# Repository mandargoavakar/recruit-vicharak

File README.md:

Discrete Class D Audio Amplifier Design
Project Overview
This project involves the design, simulation, and PCB layout of a Class D Audio Amplifier using discrete components. The circuit utilizes an NE555 timer for PWM generation and an LM741 Op-Amp as a comparator to process audio signals.
1. Circuit Design & Logic
The amplifier operates on the principle of Pulse Width Modulation (PWM) to achieve high efficiency.
·	PWM Generation (NE555): The NE555 timer is configured as an astable multivibrator to generate a high-frequency carrier wave. With $R_1=1\text{k}\Omega$, $R_2=3.3\text{k}\Omega$, and $C_1=1\text{nF}$, the switching frequency is approximately 180kHz, well above the human hearing range.
·	Comparator Stage (LM741): The LM741 compares the $1\text{kHz}$ audio input against the high-frequency carrier wave to produce a PWM signal where the pulse width is proportional to the audio amplitude.
·	Low-Pass LC Filter: A second-order filter consisting of a $22\mu\text{H}$ inductor ($L_1$) and a $1\mu\text{F}$ capacitor ($C_3$) is used at the output. It has a cutoff frequency of approximately 34kHz, effectively stripping the high-frequency carrier to recover the original audio signal.
2. Simulation Results
The circuit was verified using the built-in SPICE simulator in KiCad.
·	Audio Recovery: The simulation successfully demonstrates the recovery of a $1\text{kHz}$ sine wave from the PWM signal.
·	Transient Response: A brief startup transient is observed before the signal reaches a clean steady-state output.
3. PCB Specifications
The physical board was designed with manufacturing and reliability in mind.
·	Layers: 2-Layer through-hole design.
·	Netclass & Trace Widths:
·	Power/GND: Assigned a width of 0.8mm to handle current and ensure voltage stability.
·	Signal: Assigned a width of 0.25mm for standard audio and timing connections.
·	Board Dimensions: Approximately 50mm x 50mm with connectors (J1-J3) placed at the edges for easy interfacing.
·	DRC Verification: The board passed the Design Rules Check with 0 Errors and 0 Unconnected Items.
4. Component List (BOM)
Component	Value/Part	Footprint
U1	NE555P	DIP-8_W7.62mm
U2	LM741	DIP-8_W7.62mm
L1	22uH	L_Axial_L9.5mm_D4.0mm_P15.24mm
C3	1uF	C_Disc_D5.0mm_W2.5mm_P5.00mm
J1, J2, J3	2-Pin Conn	PinHeader_1x02_P2.54mm_Vertical

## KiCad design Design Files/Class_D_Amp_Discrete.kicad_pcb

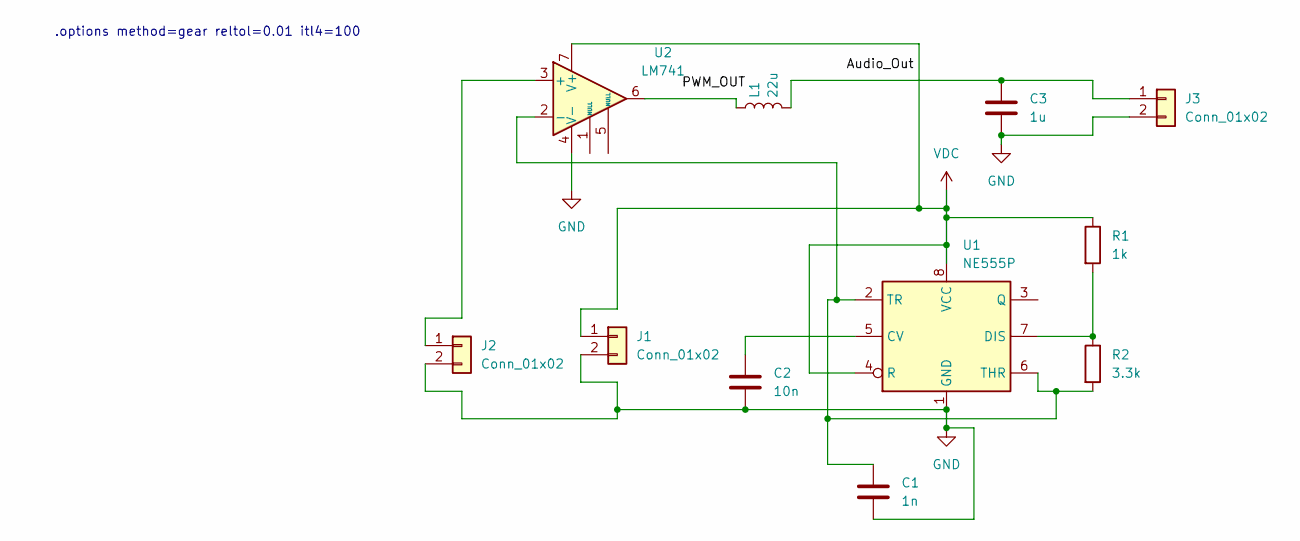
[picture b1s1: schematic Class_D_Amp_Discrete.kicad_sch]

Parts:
C1: 1n; C_Disc_D5.0mm_W2.5mm_P5.00mm
C2: 10n; C_Disc_D5.0mm_W2.5mm_P5.00mm
C3: 1u; C_Disc_D5.0mm_W2.5mm_P5.00mm
J1, J2, J3: Conn_01x02; PinHeader_1x02_P2.54mm_Vertical
L1: 22u; L_Axial_L9.5mm_D4.0mm_P15.24mm_Horizontal_Fastron_SMCC
R1: 1k; R_Axial_DIN0207_L6.3mm_D2.5mm_P7.62mm_Horizontal
R2: 3.3k; R_Axial_DIN0207_L6.3mm_D2.5mm_P7.62mm_Horizontal
U1: NE555P; DIP-8_W7.62mm
U2: LM741; DIP-8_W7.62mm

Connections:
GND: C1.2, C2.2, C3.2, J1.2, J2.2, J3.2, U1.1 (GND), U2.4 (V-)
unnamed: J2.1, U2.3 (+)
unnamed: C3.1, J3.1, L1.2
unnamed: L1.1, U2.6
unnamed: C2.1, U1.5 (CV)
unnamed: R1.2, R2.1, U1.7 (DIS)
unnamed: C1.1, R2.2, U1.2 (TR), U1.6 (THR), U2.2 (-)
VDC: J1.1, R1.1, U1.4 (R), U1.8 (VCC), U2.7 (V+)

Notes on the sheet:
.options method=gear reltol=0.01 itl4=100

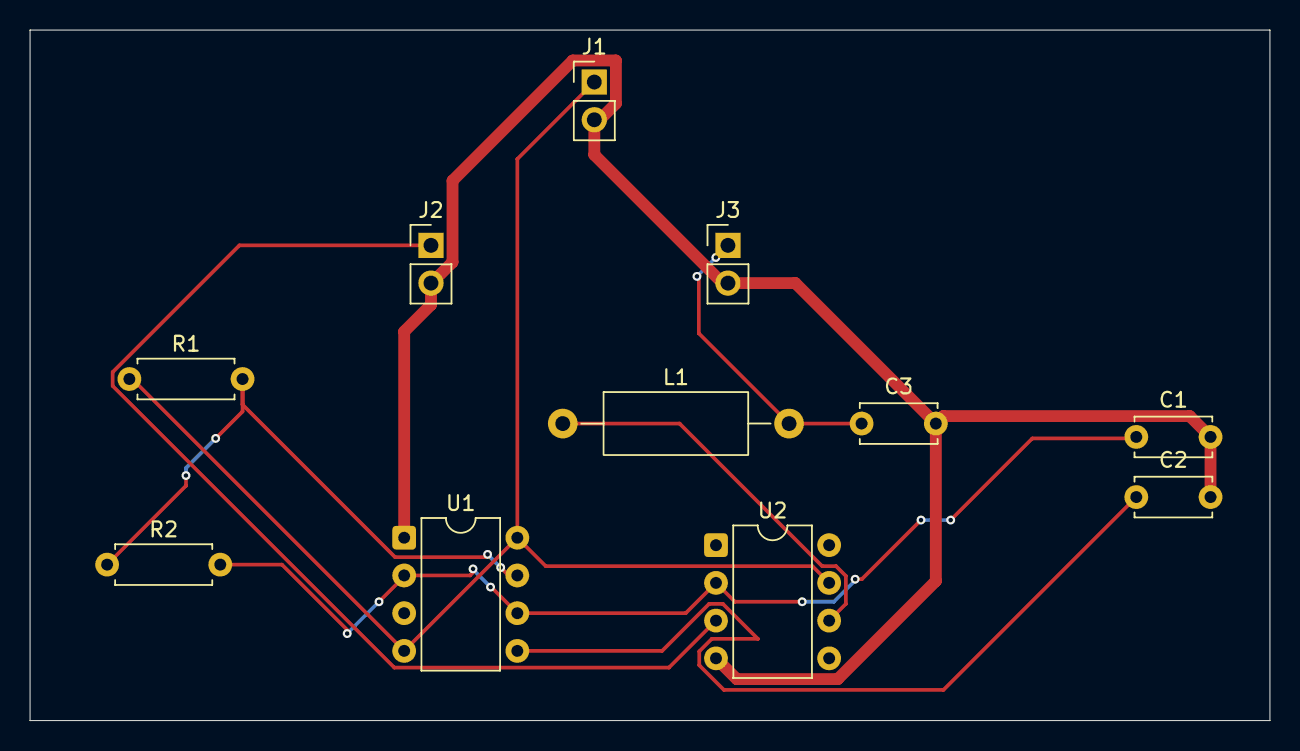
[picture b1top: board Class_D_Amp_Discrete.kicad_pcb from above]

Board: 2 copper layers, 83.5 x 46.5 mm, 11 parts (0 on the bottom side), 8 nets.

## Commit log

2025-12-18 Enhance README with project details and specifications
    Added detailed project overview, circuit design, simulation results, PCB specifications, and component list for the Class D Audio Amplifier.
